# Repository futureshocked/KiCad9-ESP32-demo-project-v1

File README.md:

# KiCad 9 ESP32 demo project, iteration 1 (archived)

> **For building, studying or modifying the board, use iteration 2:**
> **[KiCad9-ESP32-demo-project-v2-KiCad10](https://github.com/futureshocked/KiCad9-ESP32-demo-project-v2-KiCad10)**
>
> This repository holds iteration 1 in two versions: the original files from the lectures, which contain known errors, and a focused repair of the most important of those errors.

This repository holds the first iteration of the ESP32 sensor board that I design in the KiCad 9 video lectures. I keep it so that you can follow the lectures with the same files you see on screen, and so that the history of the project is preserved.

## Versions in this repository

| Version | Where to find it | KiCad version | Contents |
|---|---|---|---|
| **v1.1-repaired** | The `main` branch, or the [v1.1-repaired release](https://github.com/futureshocked/KiCad9-ESP32-demo-project-v1/releases/tag/v1.1-repaired) | KiCad 10 or later | Iteration 1 with the focused repair shown in the repair video |
| **v1.0-original** | The [v1.0-original release](https://github.com/futureshocked/KiCad9-ESP32-demo-project-v1/releases/tag/v1.0-original) | KiCad 9 or later | Iteration 1 exactly as it was at the end of the original lectures, including all the errors described below |

If you are following the original lectures in KiCad 9, download **v1.0-original** from its release page. The repaired files were saved in KiCad 10 and cannot be opened in KiCad 9.

## About the project

The board is a battery-powered environmental sensor built around the ESP32-C3. It is a four-layer PCB, about 80 × 54 mm, and includes:

1. An ESP32-C3-WROOM-02 module (U3) with Wi-Fi and Bluetooth LE.
2. A USB-C connector with a CP2102N USB-to-UART bridge (U4), USBLC6-2SC6 ESD protection (U5) and boot/reset circuitry (Q2, Q3).
3. An MCP73871 Li-ion charger with power-path management (U1) and an LM1117 3.3 V regulator (VR1).
4. A BME280 temperature, humidity and pressure sensor (U2).
5. A TEMT6000 ambient light sensor (Q1).
6. An electret microphone with a MAX4466 amplifier (U7, MK1).
7. A microSD card slot (J3) and a W25Q32 SPI flash chip (U6).
8. A header for an I2C OLED display, status LEDs, and Boot and Reset buttons.

## Two repositories, and why

There are two repositories for this project:

| Repository | Contents | Use it to |
|---|---|---|
| **KiCad9-ESP32-demo-project-v1** (this one) | Iteration 1: the original KiCad 9 files and a focused repair | Follow the original lectures and the repair video, and see how the project developed |
| **[KiCad9-ESP32-demo-project-v2-KiCad10](https://github.com/futureshocked/KiCad9-ESP32-demo-project-v2-KiCad10)** | Iteration 2, corrected and updated in KiCad 10 | Study, modify or manufacture the board |

I have kept both so that the history of the project stays intact, while anyone who wants to experiment with the design, or have it made, has a clean and correct version to start from.

## The focused repair (v1.1-repaired)

After a student reported errors in the iteration 1 PCB, I recorded a video that repairs iteration 1. As I explain in the video, this is a **focused repair** of U2, U4 and the microphone output (MIC_OUT). The remaining repairs, and several improvements, are made in iteration 2, and I do not plan any further work on iteration 1.

The repair made these changes:

1. **U2, U4, U5 and C15 are connected correctly** (issue 1 below). The PCB was updated from the schematic, the +3.3V tracks to the wrong pads were removed, and the pads were rerouted to GND, USB D- and VBUS sense. D- is routed at 0.2 mm next to D+.
2. **MIC_OUT moved from GPIO5 to GPIO0** (issue 3 below). The schematic and PCB were changed so that MIC_OUT goes to U3 pin 18 (GPIO0, on ADC1) and CS_SD goes to U3 pin 4 (GPIO5).

A DRC of the repaired board, with "Test for parity between PCB and schematic" enabled, reports no net conflicts and no unconnected pads.

The repair deliberately leaves the following as they are. If you need any of them, use iteration 2:

1. **The automatic reset and download mode circuit** (issue 2 below) is unchanged and still does not work. See [Uploading firmware](#uploading-firmware).
2. **The improvements made in iteration 2** are not included.
3. **The mounting hole and the two logos were removed.** Running Update PCB from Schematic with "Delete footprints with no symbols" ticked deleted the 2.5 mm mounting hole at the left of the board, the TE Connectivity logo and the KiCad logo, because none of them has a schematic symbol. They were not put back. Iteration 2 has all three.
4. **The fabrication files are from the original board.** The Gerbers (`ESP32PRoject_Gerber/` and `ESP32PRoject_Gerber.zip`) and the placement files (`*.pos`) were generated before the repair and still contain the errors. Do not send them to a fabricator.
5. **The `net_conflict` check is still set to Warning** in Board Setup. See issue 1 for why this matters.

## Issues found in the original iteration 1

### 1. The PCB is out of sync with the schematic (U2, U4, U5, C15)

**Status: fixed in v1.1-repaired and in iteration 2.**

The schematic is correct, but the PCB was not updated from it. Nine pads that should be on GND, USB D- or the VBUS sense net are on +3.3V instead, and +3.3V tracks are routed to them:

| Part and pad | Pin function | Net in the original PCB | Correct net |
|---|---|---|---|
| U4 (CP2102N) pad 3 | GND | +3.3V | GND |
| U4 pad 12 | GND | +3.3V | GND |
| U4 pad 21 (exposed pad) | GND | +3.3V | GND |
| U4 pad 5 | USB D- | +3.3V | /ESP32-C3-02/USB_D- |
| U4 pad 8 | VBUS sense | +3.3V | Net-(U4-VBUS) |
| U5 (USBLC6) pad 1 | I/O1, D- side | +3.3V | /ESP32-C3-02/USB_D- |
| U2 (BME280) pad 5 | SDO (I2C address select) | +3.3V | GND |
| U2 pad 7 | GND | +3.3V | GND |
| C15 pad 2 | GND | +3.3V | GND |

A board made from the original files would have the following faults:

1. All three of the CP2102N's ground pins are on +3.3V and its D- line is tied to 3.3 V, so the board would not appear as a USB serial port.
2. The BME280's pin 1 is correctly grounded, but its other ground pin, pin 7, is on +3.3V. If the two ground pins are joined inside the package, as ground pins normally are, this shorts the 3.3 V supply to ground through the sensor, which would likely damage it.
3. The BME280's SDO pin (pin 5) sets its I2C address. The schematic ties it to GND for address 0x76, but on the PCB it is on +3.3V, which selects address 0x77.
4. C15, the BME280 decoupling capacitor, has both pads on +3.3V, so it does nothing.

**Why DRC did not catch it.** In this project's Board Setup, the `net_conflict` check ("Pad net doesn't match schematic") is set to *Warning*. A DRC run with "Test for parity between PCB and schematic" enabled does list all nine pads, but only under warnings. If you look only at errors, the board appears clean.

### 2. Automatic reset and download mode do not work

**Status: not fixed in v1.1-repaired. Partly fixed in iteration 2, but still not working.**

The auto-program circuit (Q2, Q3, R33, R34) is meant to let the CP2102N's DTR and RTS signals reset the ESP32-C3 and put it into download mode, so that you can upload firmware without pressing any buttons. It has two faults:

1. **Q3 is wired backwards.** The schematic and PCB connect Q3's emitter to BOOT and its collector to DTR, which is the reverse of Q2 and of Espressif's reference circuit. Iteration 2 corrects this.
2. **The CP2102N has no DTR output.** This design uses the 20-pin QFN package of the CP2102N, which has no DTR pin. The net named DTR is connected to U4 pin 15, which is CTS, an input (see table 5.3 of the CP2102N datasheet in `Datasheets/`). Nothing drives the DTR net. This is the same in iteration 2, and I have not yet decided whether to change it.

Neither automatic reset nor automatic download mode can be relied on. DRC cannot detect either fault, because the schematic and PCB agree with each other. See [Uploading firmware](#uploading-firmware) for two ways to program the board anyway.

### 3. The microphone output is on an ADC2 pin

**Status: fixed in v1.1-repaired and in iteration 2.**

In the original files, the MAX4466 output (MIC_OUT) is connected to GPIO5, the only ADC2 pin on the ESP32-C3. Espressif's ESP32-C3 errata says ADC2 can become inoperative and recommends using ADC1 instead, and recent versions of ESP-IDF disable ADC2 on this chip by default. ADC2 is also shared with Wi-Fi. The fix moves MIC_OUT to GPIO0 (ADC1) and CS_SD to GPIO5.

## Improvements in iteration 2

Besides the fixes above, iteration 2 includes these changes, which are not part of the iteration 1 repair:

1. A PTC fuse (F2) on the +5 V output of the charger.
2. A trimmer (R17) to adjust the microphone gain, with new values for R30 (1 kΩ), R31 (22 kΩ) and C19 (10 µF).
3. The light sensor was rearranged so that its output rises with light: Q1's collector now goes to +3.3V and R23 pulls the output down to GND. In iteration 1 the output falls as light increases.
4. Three extra capacitors: C23 (100 nF decoupling) and C24 and C25 (10 nF filtering on the light sensor signal).
5. The Boot and Reset buttons (S1, S2) were rotated 180°, and the right edge of the board moved about 0.8 mm.

## Repairing the original files yourself

If you want to repeat the repair as an exercise, download **v1.0-original** and follow the repair video. In outline:

1. Open the PCB and run **Tools → Update PCB from Schematic** (F8). This moves the nine pads to their correct nets. **Untick "Delete footprints with no symbols"** in the update dialog, or the mounting hole and the two logos will be deleted.
2. Delete the +3.3V tracks and vias that still end on those pads. After the update they will appear as shorts.
3. Route GND to U4 pads 3, 12 and 21, U2 pads 5 and 7, and C15 pad 2. Route D- from U4 pad 5 to U5 pad 1 as a differential pair with D+, and connect U4 pad 8 to the VBUS sense divider (R12, R13, C11).
4. To fix the microphone output, swap the MIC_OUT and CS_SD connections on U3 in the schematic, update the PCB again, and reroute both nets.
5. Run DRC with **Test for parity between PCB and schematic** enabled, and check the warnings as well as the errors. You can also set `net_conflict` to *Error* in Board Setup → Design Rules → Violation Severity.

## Uploading firmware

Because automatic reset and download mode do not work, use one of these two methods to upload firmware. Both work on every version of iteration 1 and on iteration 2:

1. **Through the USB-C connector and the CP2102N, with the buttons.** Hold **Boot** (S1), press and release **Reset** (S2), then release **Boot**. The ESP32-C3 starts in download mode and you can upload. Press **Reset** afterwards to run the new firmware. Serial monitoring through the CP2102N works normally.
2. **Through the ESP32-C3's built-in USB Serial/JTAG controller.** The ESP32-C3 has its own USB interface on GPIO18 (D-) and GPIO19 (D+). On this board these pins are brought out to header **J5**: pin 3 is D-, pin 4 is D+ and pin 5 is GND. Wire a USB cable's D-, D+ and GND to those pins and power the board from the USB-C connector or the battery. **Do not connect the cable's 5 V wire to J5**: J5 pin 1 is the 3.3 V rail. Through this interface, esptool and the Arduino and ESP-IDF tools can reset the chip and enter download mode without the buttons, and you get a serial console and JTAG debugging as well. For this to keep working, your firmware must not use GPIO18 and GPIO19 as ordinary I/O.

## License

Copyright © 2025–2026, Peter Dalmaris. Licensed under the CERN-OHL-S v2.0. See [LICENSE](LICENSE).

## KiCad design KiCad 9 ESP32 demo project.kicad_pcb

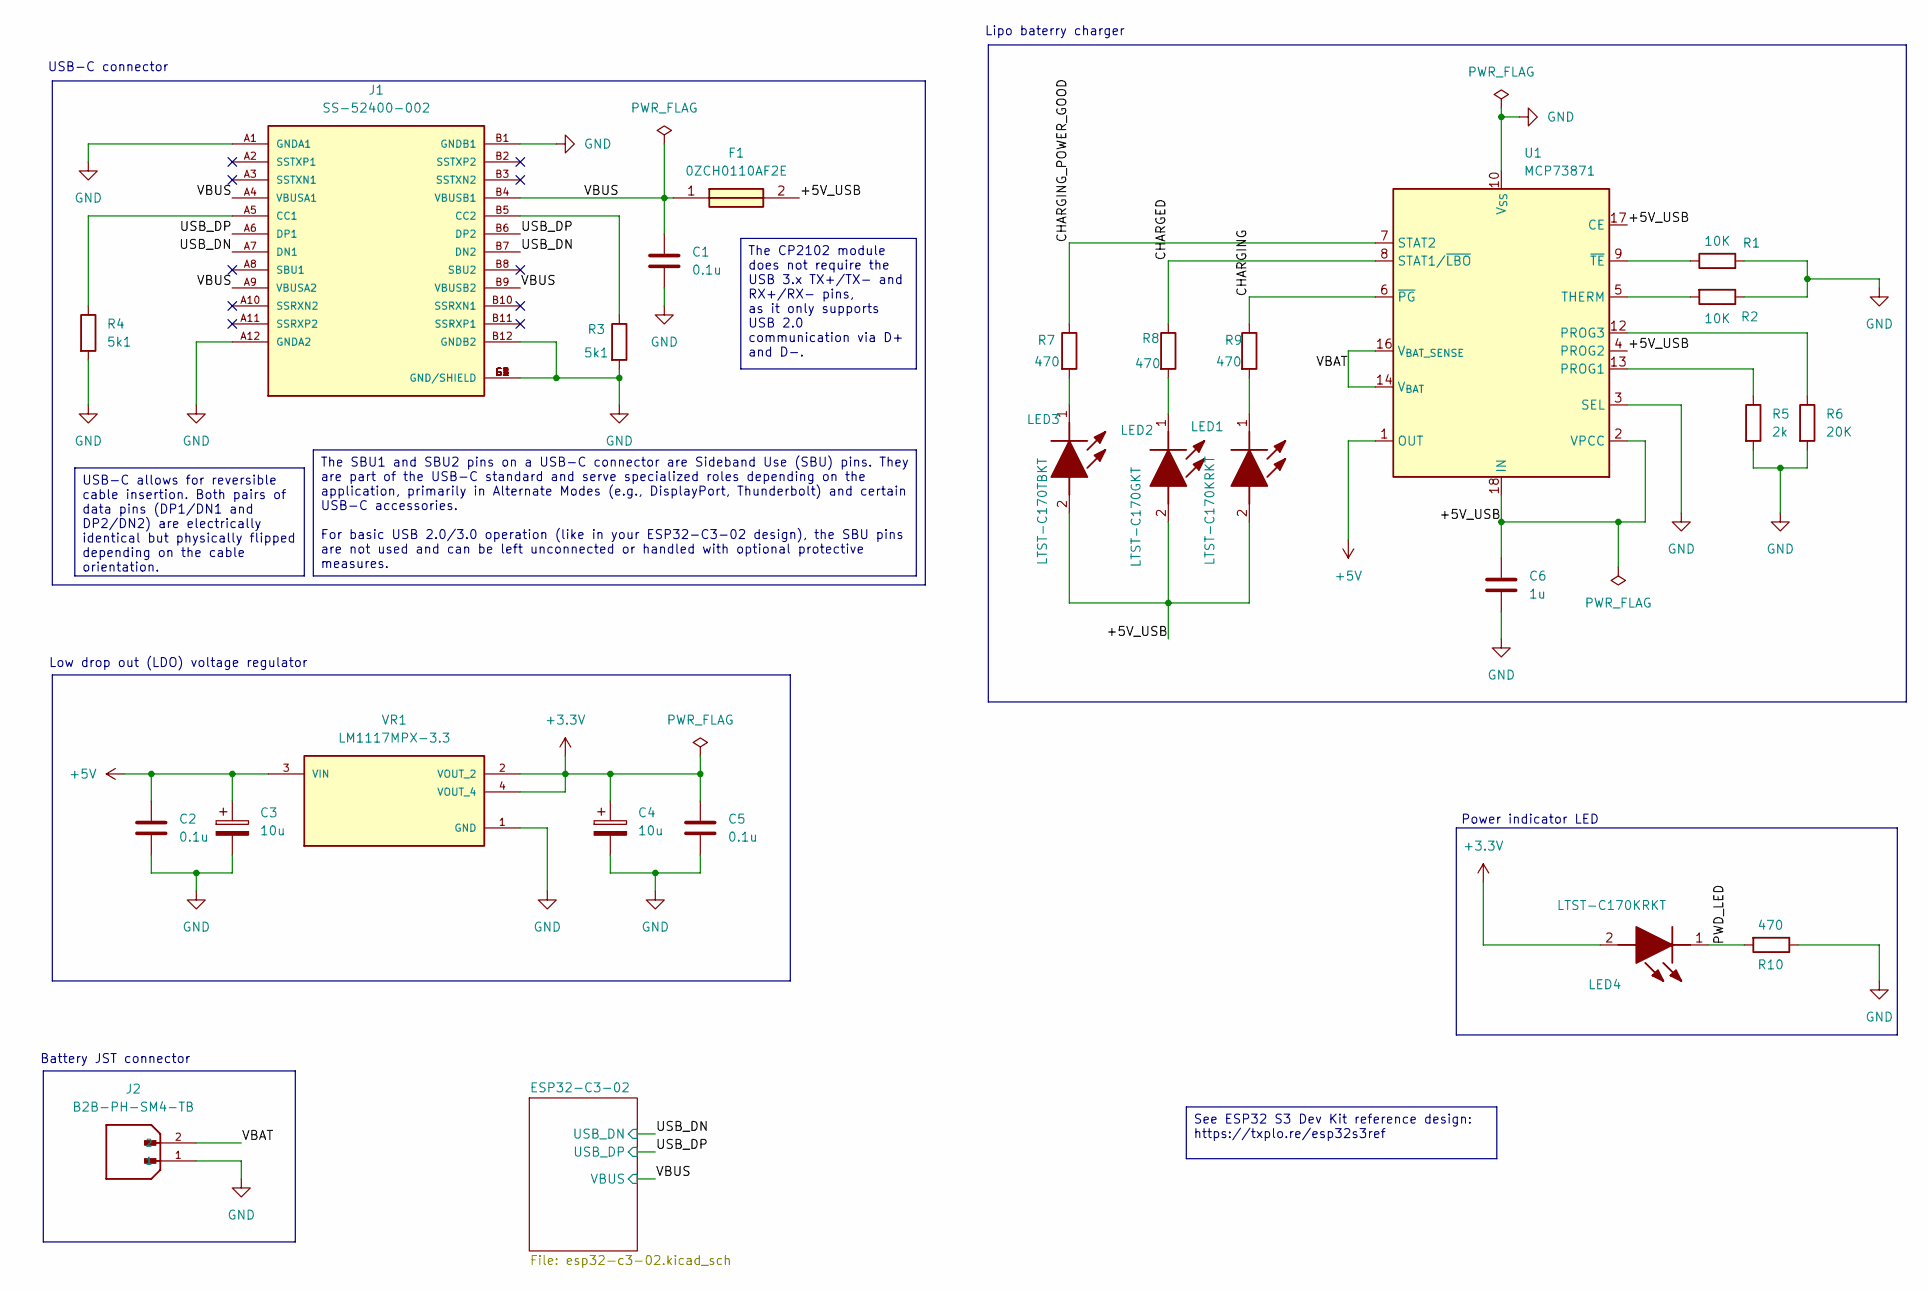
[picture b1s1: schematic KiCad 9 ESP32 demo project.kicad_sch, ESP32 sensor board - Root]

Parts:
C1, C2, C5: 0.1u; C_0805_2012Metric
C3, C4: 10u; T491A
C6: 1u; C_0805_2012Metric
F1: 0ZCH0110AF2E; FUSC3226X100N; Manufacturer_Part_Number 0ZCH0110AF2E
J1: SS-52400-002; BELFUSE_SS-52400-002; PARTREV A0
J2: B2B-PH-SM4-TB; JST_B2B-PH-SM4-TB; PARTREV N/A
LED1, LED4: LTST-C170KRKT; LEDC2012X120N; Manufacturer_Part_Number LTST-C170KRKT; Mouser Part Number 859-LTST-C170KRKT
LED2: LTST-C170GKT; LEDC2012X120N; Manufacturer_Part_Number LTST-C170GKT; Mouser Part Number 859-LTST-C170GKT
LED3: LTST-C170TBKT; LEDC2012X120N; Manufacturer_Part_Number LTST-C170TBKT; Mouser Part Number 859-LTST-C170TBKT
R1, R2: 10K; R_0805_2012Metric
R3, R4: 5k1; R_0805_2012Metric
R5: 2k; R_0805_2012Metric
R6: 20K; R_0805_2012Metric
R7, R8, R9, R10: 470; R_0805_2012Metric
U1: MCP73871; QFN-20-1EP_4x4mm_P0.5mm_EP2.5x2.5mm
VR1: LM1117MPX-3.3; VREG_LM1117MPX-3.3

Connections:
+3.3V: C4.1, C5.1, LED4.2 (A), VR1.2 (VOUT_2), VR1.4 (VOUT_4); also elsewhere on the board
+5V: C2.1, C3.1, U1.1 (OUT), U1.20 (OUT), VR1.3 (VIN)
/+5V_USB: C6.1, F1.2, LED1.2 (A), LED2.2 (A), LED3.2 (A), U1.2 (VPCC), U1.4 (PROG2), U1.17 (CE), U1.18 (IN), U1.19 (IN)
/CHARGED: R8.1, U1.8 (STAT1/~LBO)
/CHARGING: R9.1, U1.6 (~PG)
/CHARGING_POWER_GOOD: R7.1, U1.7 (STAT2)
/PWD_LED: LED4.1 (K), R10.2
/USB_DN: J1.A7 (DN1), J1.B7 (DN2); also elsewhere on the board
/USB_DP: J1.A6 (DP1), J1.B6 (DP2); also elsewhere on the board
/VBAT: J2.2, U1.14 (V_{BAT}), U1.15 (V_{BAT}), U1.16 (V_{BAT_SENSE})
/VBUS: C1.1, F1.1, J1.A4 (VBUSA1), J1.A9 (VBUSA2), J1.B4 (VBUSB1), J1.B9 (VBUSB2); also elsewhere on the board
GND: C1.2, C2.2, C3.2, C4.2, C5.2, C6.2, J1.A1 (GNDA1), J1.A12 (GNDA2), J1.B1 (GNDB1), J1.B12 (GNDB2), J1.G1 (GND/SHIELD), J1.G2 (GND/SHIELD), J1.G3 (GND/SHIELD), J1.G4 (GND/SHIELD), J1.S1 (GND/SHIELD), J1.S2 (GND/SHIELD), J1.S3 (GND/SHIELD), J1.S4 (GND/SHIELD), J2.1, R1.2, R2.1, R3.2, R4.2, R5.2, R6.2, R10.1, U1.3 (SEL), U1.10 (V_{SS}), U1.11 (V_{SS}), U1.21 (V_{SS}), VR1.1 (GND); also elsewhere on the board
unnamed: J1.A5 (CC1), R4.1
unnamed: J1.B5 (CC2), R3.1
unnamed: LED1.1 (K), R9.2
unnamed: LED2.1 (K), R8.2
unnamed: LED3.1 (K), R7.2
unnamed: R5.1, U1.13 (PROG1)
unnamed: R6.1, U1.12 (PROG3)
unnamed: R2.2, U1.5 (THERM)
unnamed: R1.1, U1.9 (~TE)

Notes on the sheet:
Lipo baterry charger
Low drop out (LDO) voltage regulator
Power indicator LED
Battery JST connector
USB-C connector
See ESP32 S3 Dev Kit reference design: https://txplo.re/esp32s3ref
The CP2102 module does not require the USB 3.x TX+/TX- and RX+/RX- pins, as it only supports USB 2.0 communication via D+ and D-.
USB-C allows for reversible cable insertion. Both pairs of data pins (DP1/DN1 and DP2/DN2) are electrically identical but physically flipped depending on the cable orientation.
The SBU1 and SBU2 pins on a USB-C connector are Sideband Use (SBU) pins. They are part of the USB-C standard and serve specialized roles depending on the application, primarily in Alternate Modes (e.g., DisplayPort, Thunderbolt) and certain USB-C accessories. For basic USB 2.0/3.0 operation (like i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

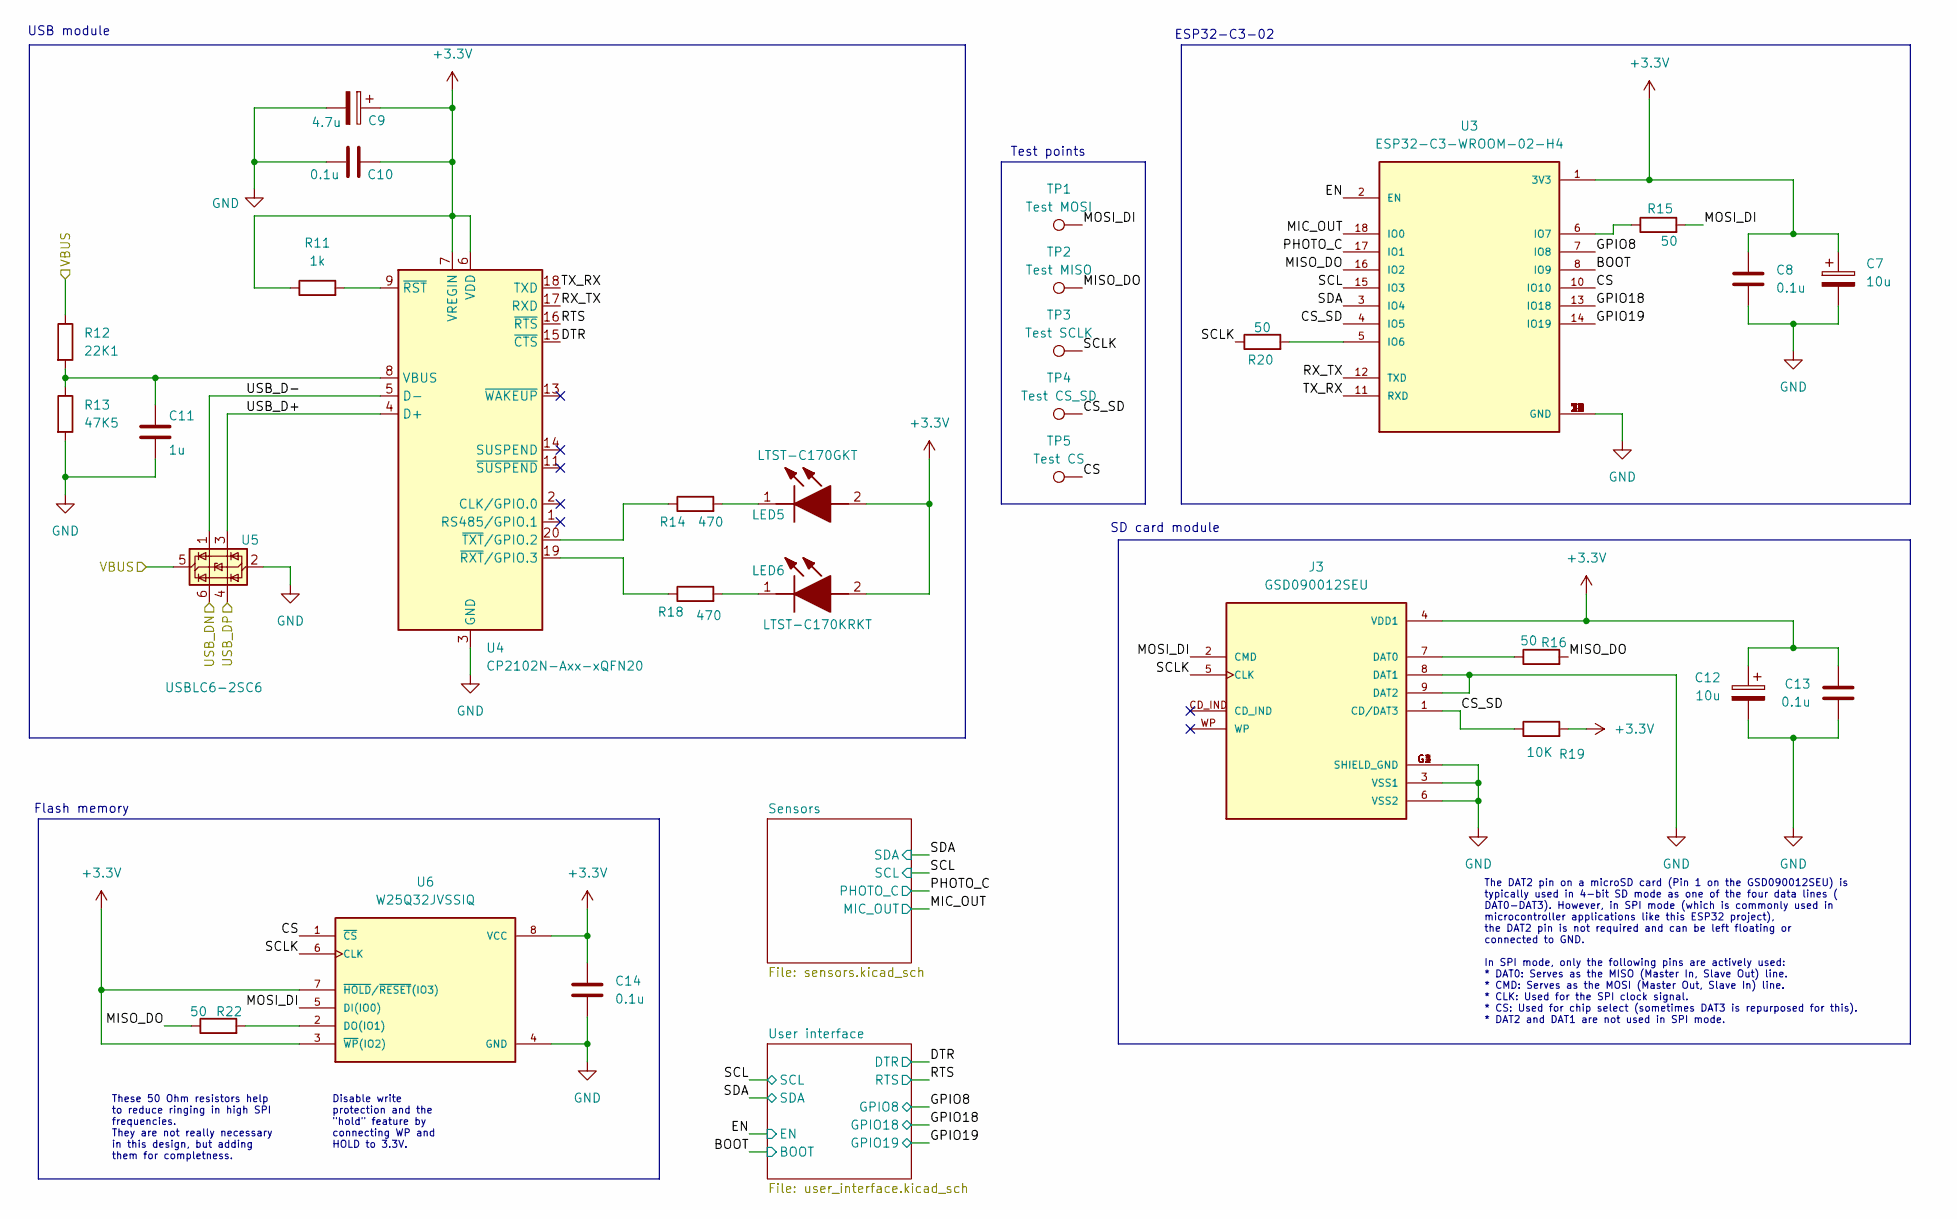
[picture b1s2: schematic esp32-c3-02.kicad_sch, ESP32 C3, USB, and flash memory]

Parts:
C7, C12: 10u; T491A
C8, C10, C13, C14: 0.1u; C_0805_2012Metric
C9: 4.7u; T491A
C11: 1u; C_0805_2012Metric
J3: GSD090012SEU; AMPHENOL_GSD090012SEU; PARTREV E
LED5: LTST-C170GKT; LEDC2012X120N; Manufacturer_Part_Number LTST-C170GKT; Mouser Part Number 859-LTST-C170GKT
LED6: LTST-C170KRKT; LEDC2012X120N; Manufacturer_Part_Number LTST-C170KRKT; Mouser Part Number 859-LTST-C170KRKT
R11: 1k; R_0805_2012Metric
R12: 22K1; R_0805_2012Metric
R13: 47K5; R_0805_2012Metric
R14, R18: 470; R_0805_2012Metric
R15, R16, R20, R22: 50; R_0805_2012Metric
R19: 10K; R_0805_2012Metric
TP1: Test MOSI; TestPoint_Pad_D1.0mm
TP2: Test MISO; TestPoint_Pad_D1.0mm
TP3: Test SCLK; TestPoint_Pad_D1.0mm
TP4: Test CS_SD; TestPoint_Pad_D1.0mm
TP5: Test CS; TestPoint_Pad_D1.0mm
U3: ESP32-C3-WROOM-02-H4; MODULE_ESP32-C3-WROOM-02-H4
U4: CP2102N-Axx-xQFN20; SiliconLabs_QFN-20-1EP_3x3mm_P0.5mm_EP1.8x1.8mm
U5: USBLC6-2SC6; SOT-23-6
U6: W25Q32JVSSIQ; SOIC127P790X216-8N; M_PART_NUMBER W25QXX

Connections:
+3.3V: C7.1, C8.1, C9.1, C10.2, C12.1, C13.1, C14.1, J3.4 (VDD1), LED5.2 (A), LED6.2 (A), R11.1, R19.2, U3.1 (3V3), U4.6 (VDD), U4.7 (VREGIN), U6.3 (~WP(IO2)), U6.7 (~HOLD/~RESET(IO3)), U6.8 (VCC); also elsewhere on the board
/ESP32-C3-02/BOOT: U3.8 (IO9); also elsewhere on the board
/ESP32-C3-02/CS: TP5.1 (1_1), U3.10 (IO10), U6.1 (~CS)
/ESP32-C3-02/CS_SD: J3.1 (CD/DAT3), R19.1, TP4.1 (1_1), U3.4 (IO5)
/ESP32-C3-02/DTR: U4.15 (~CTS); also elsewhere on the board
/ESP32-C3-02/EN: U3.2 (EN); also elsewhere on the board
/ESP32-C3-02/GPIO8: U3.7 (IO8); also elsewhere on the board
/ESP32-C3-02/GPIO18: U3.13 (IO18); also elsewhere on the board
/ESP32-C3-02/GPIO19: U3.14 (IO19); also elsewhere on the board
/ESP32-C3-02/MIC_OUT: U3.18 (IO0); also elsewhere on the board
/ESP32-C3-02/MISO_DO: R16.2, R22.1, TP2.1 (1_1), U3.16 (IO2)
/ESP32-C3-02/MOSI_DI: J3.2 (CMD), R15.2, TP1.1 (1_1), U6.5 (DI(IO0))
/ESP32-C3-02/PHOTO_C: U3.17 (IO1); also elsewhere on the board
/ESP32-C3-02/RTS: U4.16 (~RTS); also elsewhere on the board
/ESP32-C3-02/RX_TX: U3.12 (TXD), U4.17 (RXD)
/ESP32-C3-02/SCL: U3.15 (IO3); also elsewhere on the board
/ESP32-C3-02/SCLK: J3.5 (CLK), R20.1, TP3.1 (1_1), U6.6 (CLK)
/ESP32-C3-02/SDA: U3.3 (IO4); also elsewhere on the board
/ESP32-C3-02/TX_RX: U3.11 (RXD), U4.18 (TXD)
/ESP32-C3-02/USB_D+: U4.4 (D+), U5.3 (I/O2)
/ESP32-C3-02/USB_D-: U4.5 (D-), U5.1 (I/O1)
/USB_DN: U5.6 (I/O1); also elsewhere on the board
/USB_DP: U5.4 (I/O2); also elsewhere on the board
/VBUS: R12.1, U5.5 (VBUS); also elsewhere on the board
GND: C7.2, C8.2, C9.2, C10.1, C11.2, C12.2, C13.2, C14.2, J3.3 (VSS1), J3.6 (VSS2), J3.8 (DAT1), J3.9 (DAT2), J3.G1 (SHIELD_GND), J3.G2 (SHIELD_GND), J3.G3 (SHIELD_GND), J3.G4 (SHIELD_GND), R13.2, U3.9 (GND), U3.19 (GND), U3.20 (GND), U3.21 (GND), U3.22 (GND), U3.23 (GND), U3.24 (GND), U3.25 (GND), U3.26 (GND), U3.27 (GND), U3.28 (GND), U3.29 (GND), U3.30 (GND), U3.31 (GND), U3.32 (GND), U3.33 (GND), U3.34 (GND), U3.35 (GND), U3.36 (GND), U3.37 (GND), U3.38 (GND), U3.39 (GND), U4.3 (GND), U4.12 (GND), U4.21 (GND), U5.2 (GND), U6.4 (GND); also elsewhere on the board
unnamed: J3.7 (DAT0), R16.1
unnamed: LED5.1 (K), R14.2
unnamed: LED6.1 (K), R18.2
unnamed: R20.2, U3.5 (IO6)
unnamed: R15.1, U3.6 (IO7)
unnamed: C11.1, R12.2, R13.1, U4.8 (VBUS)
unnamed: R11.2, U4.9 (~RST)
unnamed: R18.1, U4.19 (~RXT/GPIO.3)
unnamed: R14.1, U4.20 (~TXT/GPIO.2)
unnamed: R22.2, U6.2 (DO(IO1))

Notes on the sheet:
USB module
SD card module
Flash memory
ESP32-C3-02
Test points
These 50 Ohm resistors help to reduce ringing in high SPI frequencies. They are not really necessary in this design, but adding them for completness.
The DAT2 pin on a microSD card (Pin 1 on the GSD090012SEU) is typically used in 4-bit SD mode as one of the four data lines ( DAT0-DAT3). However, in SPI mode (which is commonly used in microcontroller applications like this ESP32 project), the DAT2 pin is not required and can be left floating or c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
Disable write protection and the "hold" feature by connecting WP and HOLD to 3.3V.

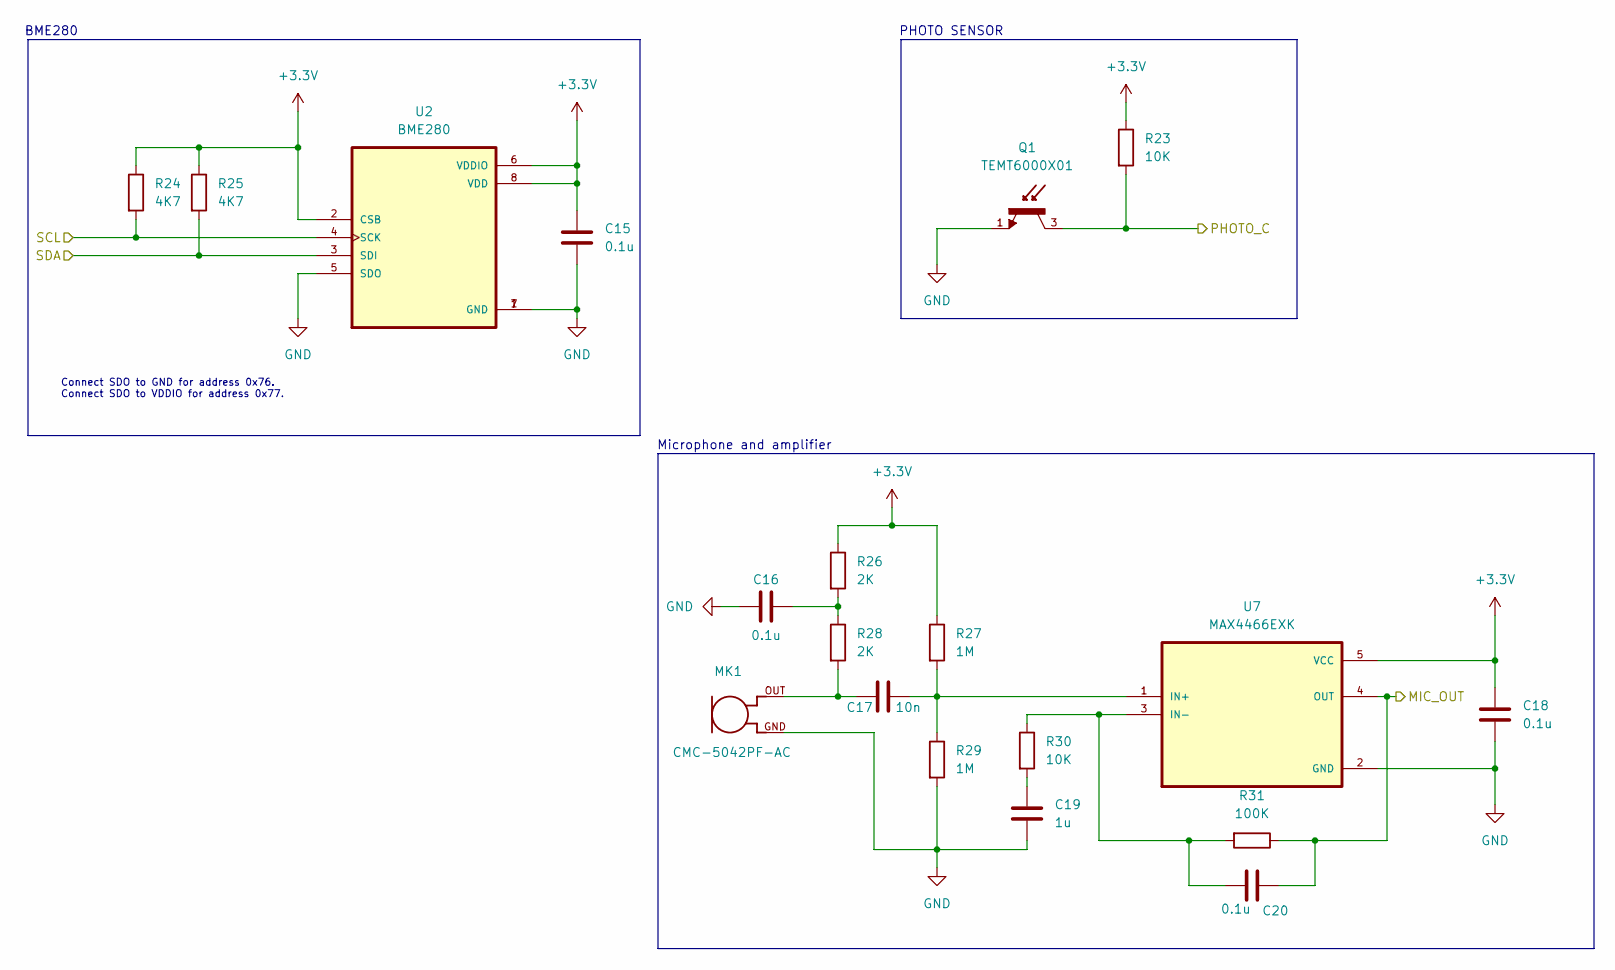
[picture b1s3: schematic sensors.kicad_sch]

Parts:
C15, C16, C18, C20: 0.1u; C_0805_2012Metric
C17: 10n; C_0805_2012Metric
C19: 1u; C_0805_2012Metric
MK1: CMC-5042PF-AC; CUI_CMC-5042PF-AC
Q1: TEMT6000X01; TRANS_TEMT6000X01; PARTREV 1.9
R23, R30: 10K; R_0805_2012Metric
R24, R25: 4K7; R_0805_2012Metric
R26, R28: 2K; R_0805_2012Metric
R27, R29: 1M; R_0805_2012Metric
R31: 100K; R_0805_2012Metric
U2: BME280; PSON65P250X250X100-8N
U7: MAX4466EXK; SOT65P210X110-5N

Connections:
+3.3V: C15.1, C18.1, R23.1, R24.1, R25.1, R26.1, R27.1, U2.2 (CSB), U2.6 (VDDIO), U2.8 (VDD), U7.5 (VCC); also elsewhere on the board
/ESP32-C3-02/MIC_OUT: C20.1, R31.1, U7.4 (OUT); also elsewhere on the board
/ESP32-C3-02/PHOTO_C: Q1.3, R23.2; also elsewhere on the board
/ESP32-C3-02/SCL: R24.2, U2.4 (SCK); also elsewhere on the board
/ESP32-C3-02/SDA: R25.2, U2.3 (SDI); also elsewhere on the board
GND: C15.2, C16.2, C18.2, C19.2, MK1.GND, Q1.1, R29.2, U2.1 (GND), U2.5 (SDO), U2.7 (GND), U7.2 (GND); also elsewhere on the board
unnamed: C16.1, R26.2, R28.1
unnamed: C17.2, MK1.OUT, R28.2
unnamed: C19.1, R30.2
unnamed: C17.1, R27.2, R29.1, U7.1 (IN+)
unnamed: C20.2, R30.1, R31.2, U7.3 (IN-)

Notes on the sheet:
Microphone and amplifier
PHOTO SENSOR
BME280
Connect SDO to GND for address 0x76. Connect SDO to VDDIO for address 0x77.

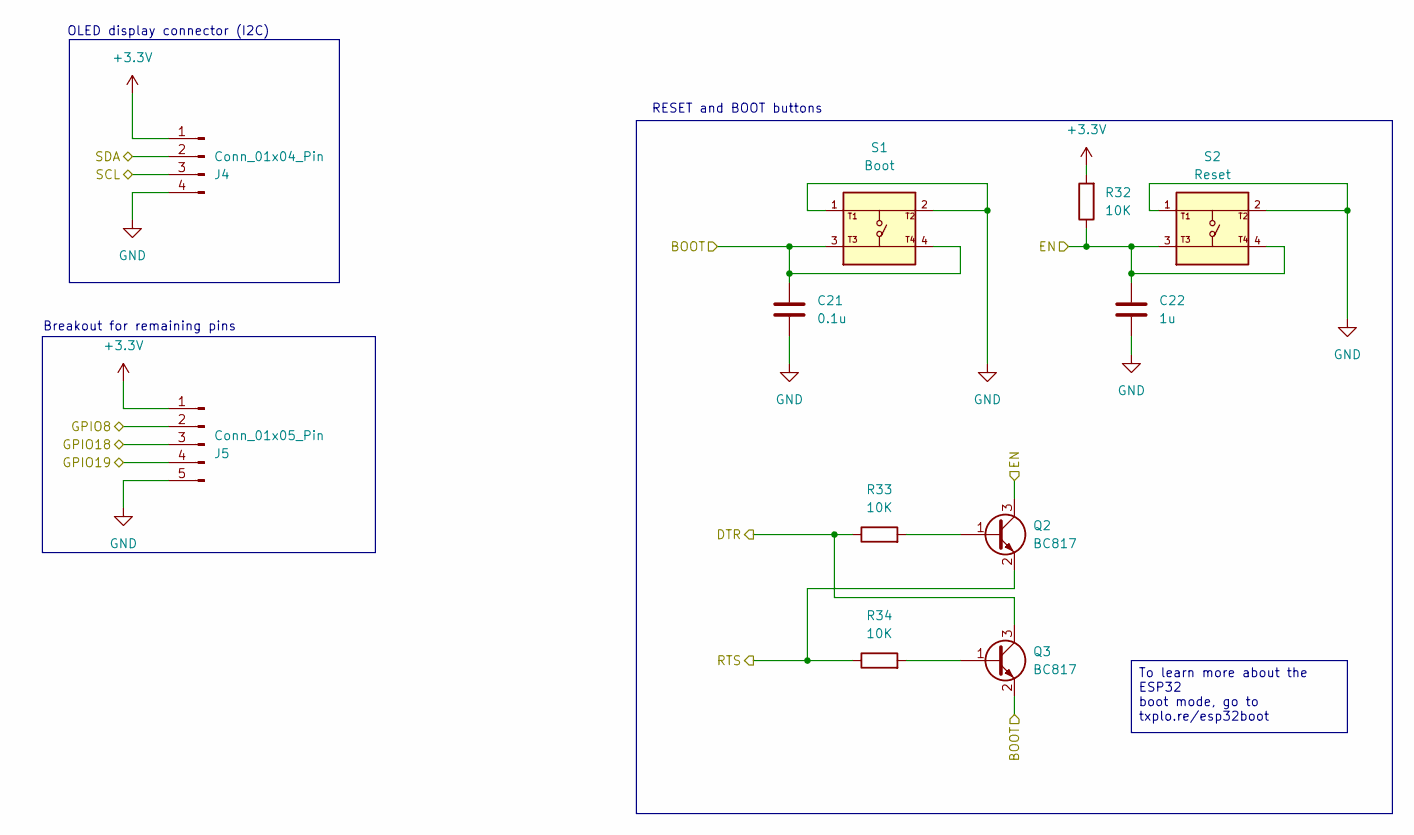
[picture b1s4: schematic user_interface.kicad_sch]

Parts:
C21: 0.1u; C_0805_2012Metric
C22: 1u; C_0805_2012Metric
J4: Conn_01x04_Pin; PinHeader_1x04_P2.54mm_Vertical
J5: Conn_01x05_Pin; PinHeader_1x05_P2.54mm_Vertical
Q2, Q3: BC817; SOT-23
R32, R33, R34: 10K; R_0805_2012Metric
S1: Boot; SW_USLPT2819DT2TR; PARTREV P
S2: Reset; SW_USLPT2819DT2TR; PARTREV P

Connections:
+3.3V: J4.1, J5.1, R32.2; also elsewhere on the board
/ESP32-C3-02/BOOT: C21.1, Q3.2 (E), S1.3, S1.4; also elsewhere on the board
/ESP32-C3-02/DTR: Q3.3 (C), R33.1; also elsewhere on the board
/ESP32-C3-02/EN: C22.1, Q2.3 (C), R32.1, S2.3, S2.4; also elsewhere on the board
/ESP32-C3-02/GPIO8: J5.2; also elsewhere on the board
/ESP32-C3-02/GPIO18: J5.3; also elsewhere on the board
/ESP32-C3-02/GPIO19: J5.4; also elsewhere on the board
/ESP32-C3-02/RTS: Q2.2 (E), R34.1; also elsewhere on the board
/ESP32-C3-02/SCL: J4.3; also elsewhere on the board
/ESP32-C3-02/SDA: J4.2; also elsewhere on the board
GND: C21.2, C22.2, J4.4, J5.5, S1.1, S1.2, S2.1, S2.2; also elsewhere on the board
unnamed: Q2.1 (B), R33.2
unnamed: Q3.1 (B), R34.2

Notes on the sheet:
Breakout for remaining pins
RESET and BOOT buttons
OLED display connector (I2C)
To learn more about the ESP32 boot mode, go to txplo.re/esp32boot

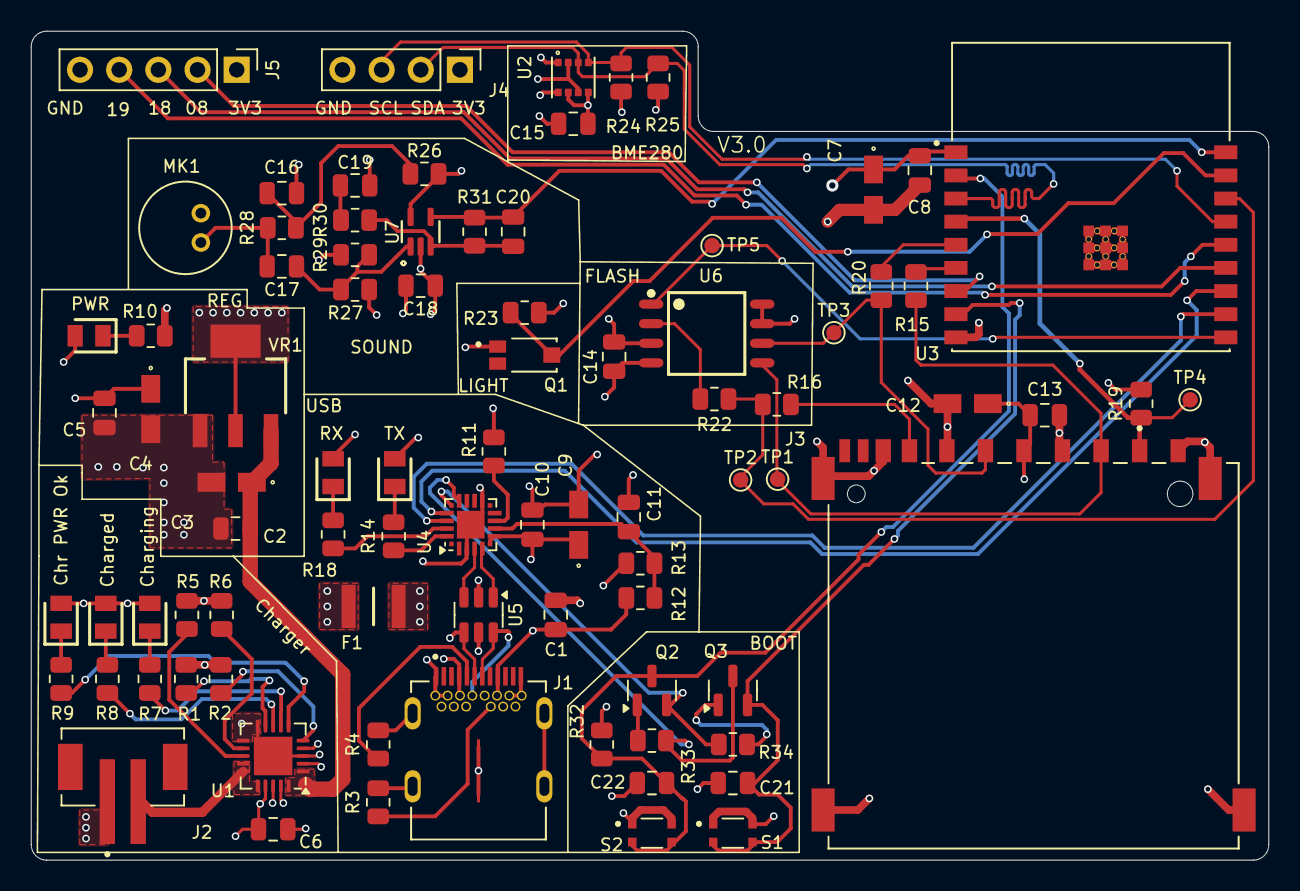
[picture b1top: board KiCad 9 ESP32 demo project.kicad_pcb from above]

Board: 4 copper layers, 80.2 x 53.8 mm, 85 parts (0 on the bottom side), 58 nets.

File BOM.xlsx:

DESIGNATOR | QTY | VALUE | MANUF. PART No | MANUFACTURER | PACKAGE | DESCRIPTION
> C1, C2, C5, C8, C10, C13-C16, C18, C20, C21 | 12 | 0.1u | C0805C104K4RAC | KEMET | 805 | Multilayer Ceramic Capacitors MLCC - SMD/SMT 16V 0.1uF X7R 0805 10%
> C3, C4, C7, C12 | 4 | 10u | T491A106K010AT7280 | KEMET | 1206 | T491, Tantalum, MnO2 Tantalum, Commercial Grade, 10 uF, 10%, 10 VDC, 125C, -55C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
> C6, C11, C19, C22 | 4 | 1u | C0805C105K4RACTU | KEMET | 805 | Multilayer Ceramic Capacitors MLCC - SMD/SMT 16V 1uF X7R 0805 10%
C9 | 1 | 4.7u | T491A475K010AT7280 | KEMET | 1206 | T491, Tantalum, MnO2 Tantalum, Commercial Grade, 4.7 uF, 10%, 10 VDC, 125C, -55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
C17 | 1 | 10n | C0805C103M4RACTU | KEMET | 805 | Multilayer Ceramic Capacitors MLCC - SMD/SMT 16V 0.01uF X7R 0805 20%
> D1, D4, D6 | 3 | RED | LTST-C170KRKT | Lite-On | 805 | Standard LEDs - SMD Red Clear 631nm
> D2, D5 | 2 | GREEN | LTST-C170GKT | Lite-On | 805 | LED,SMD,0805,Green,6mcd,130deg Lite-On LTST-C170GKT, CHIPLED 0805 Series Green 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
D3 | 1 | BLUE | LTST-C170TBKT | Lite-On | 805 | LED,SMD,0805,Blue,28mcd,130deg
F1 | 1 | 0ZCH0110AF2E | 0ZCH0110AF2E | Belfuse | 1210 | 1210 SMT PPTC | 1.10 Ih | 16V
J1 | 1 | USB_C_Receptacle | Footprints:BELFUSE_SS-52400-002 | BELFUSE Stewart Connector | SS-52400-003 for standard 1.6 mm PCB thickness | USB 2.0-only Type-C Receptacle connector. See https://www.snapeda.com/parts/SS-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
J2 | 1 | JST_2mm_LiPo | JST_B2B-PH-SM4-TB | JST |  | 2 Pin 2mm JST Battery Connector
J3 | 1 | GSD090012SEU | GSD090012SEU | Amphenol |  | Memory Card Connectors SD CARD CONNECTOR 9 POS, SMT
> J4, J5 | 2 | B4B-XH-AM | B4B-XH-AM | JST |  | Connector header vertical 4pos 2.5mm
J6 | 1 | Conn_01x05 |  |  |  | Header 1X5, 2.54mm
MK1 | 1 | CMC-5042PF-AC | CMC-5042PF-AC | CUI INC |  | Microphone
Q1 | 1 | TEMT6000X01 | TEMT6000X01 | VISHAY | 4 mm x 2 mm x 1.05 mm | Ambient Light Sensors Ambient Light Sensor AEC-Q101 Qualified
> Q2, Q3 | 2 | BC817 | BC817 |  | SOT-23 | 0.8A Ic, 45V Vce, NPN Transistor, SOT-23
> R1, R2, R19, R23, R30, R32-R34 | 8 | 10K |  |  | 805 | SMD resistor, 0805, 125mW, 1%
> R3, R4 | 2 | 5k1 |  |  | 0805 | SMD resistor, 0805, 125mW, 1%
> R5, R26, R28 | 3 | 2K |  |  | 0805 | SMD resistor, 0805, 125mW, 1%
R6 | 1 | 20K |  |  | 0805 | SMD resistor, 0805, 125mW, 1%
> R7-R9 | 3 | 470 |  |  | 0805 | SMD resistor, 0805, 125mW, 1%
> R10, R14, R18 | 3 | 330 |  |  | 0805 | SMD resistor, 0805, 125mW, 1%
R11 | 1 | 1K |  |  | 0805 | SMD resistor, 0805, 125mW, 1%
R12 | 1 | 22K1 |  |  | 0805 | SMD resistor, 0805, 125mW, 1%
R13 | 1 | 47K5 |  |  | 0805 | SMD resistor, 0805, 125mW, 1%
> R15-R17, R20-R22 | 6 | 50 |  |  | 0805 | SMD resistor, 0805, 125mW, 1%
> R24, R25 | 2 | 4K7 |  |  | 0805 | SMD resistor, 0805, 125mW, 1%
> R27, R29 | 2 | 1M |  |  | 0805 | SMD resistor, 0805, 125mW, 1%
R31 | 1 | 100K |  |  | 0805 | SMD resistor, 0805, 125mW, 1%
> SW1, SW2 | 2 | 1101NE | USLPT2819 Family | TE Connectivity | USLPT2819 MSLPT (Mini size) | SMD_6x3.5mm_h2.5mm. Please see https://www.snapeda.com/parts/USLPT2819DT2TR/TE%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
U1 | 1 | MCP73871 | MCP73871-4CCI/ML | Microchip | QFN50P400X400X100-21N | Single cell, Li-Ion/Li-Po charge management controller. See https://www.snapeda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
U2 | 1 | LM1117MPX-3.3_NOPB | LM1117MPX-33NOPB | On Semiconductor | SOT−223 CASE 318H | See https://www.snapeda.com/parts/LM1117MPX-33NOPB/ON%20Semicond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
U3 | 1 | ESP32-C3-WROOM-02-H4 | ESP32-C3-WROOM-02-H4 | Espressif |  | Multiprotocol Modules SMD module, ESP32-C3, 4MB SPI flash, PCB antenna
U4 | 1 | CP2102N-A02-GQFN20 | CP2102N-A02-GQFN20 | Silicon Laboratories | QFN20 | USB to UART Bridge
U5 | 1 | USBLC6-2SC6 | USBLC6-2SC6 | STMicroelectronics | SOT-23-6 | ESD Suppressors / TVS Diodes ESD Protection Low Cap
U6 | 1 | W25Q32JVSSIQ | W25Q32JVSSIQ | Winbond | SOIC-8 | NOR Flash spiFlash, 32M-bit, 4Kb Uniform Sector
U7 | 1 | BME280 | BME280 | Bosch | LGA-8 | Air Quality Sensor MEMS humidity, pressure and temperature sensor
U8 | 1 | MAX4466EXK+T | MAX4466EXK+T | Analog Devices Inc. | SC-70-5 | Microphone Preamplifier
